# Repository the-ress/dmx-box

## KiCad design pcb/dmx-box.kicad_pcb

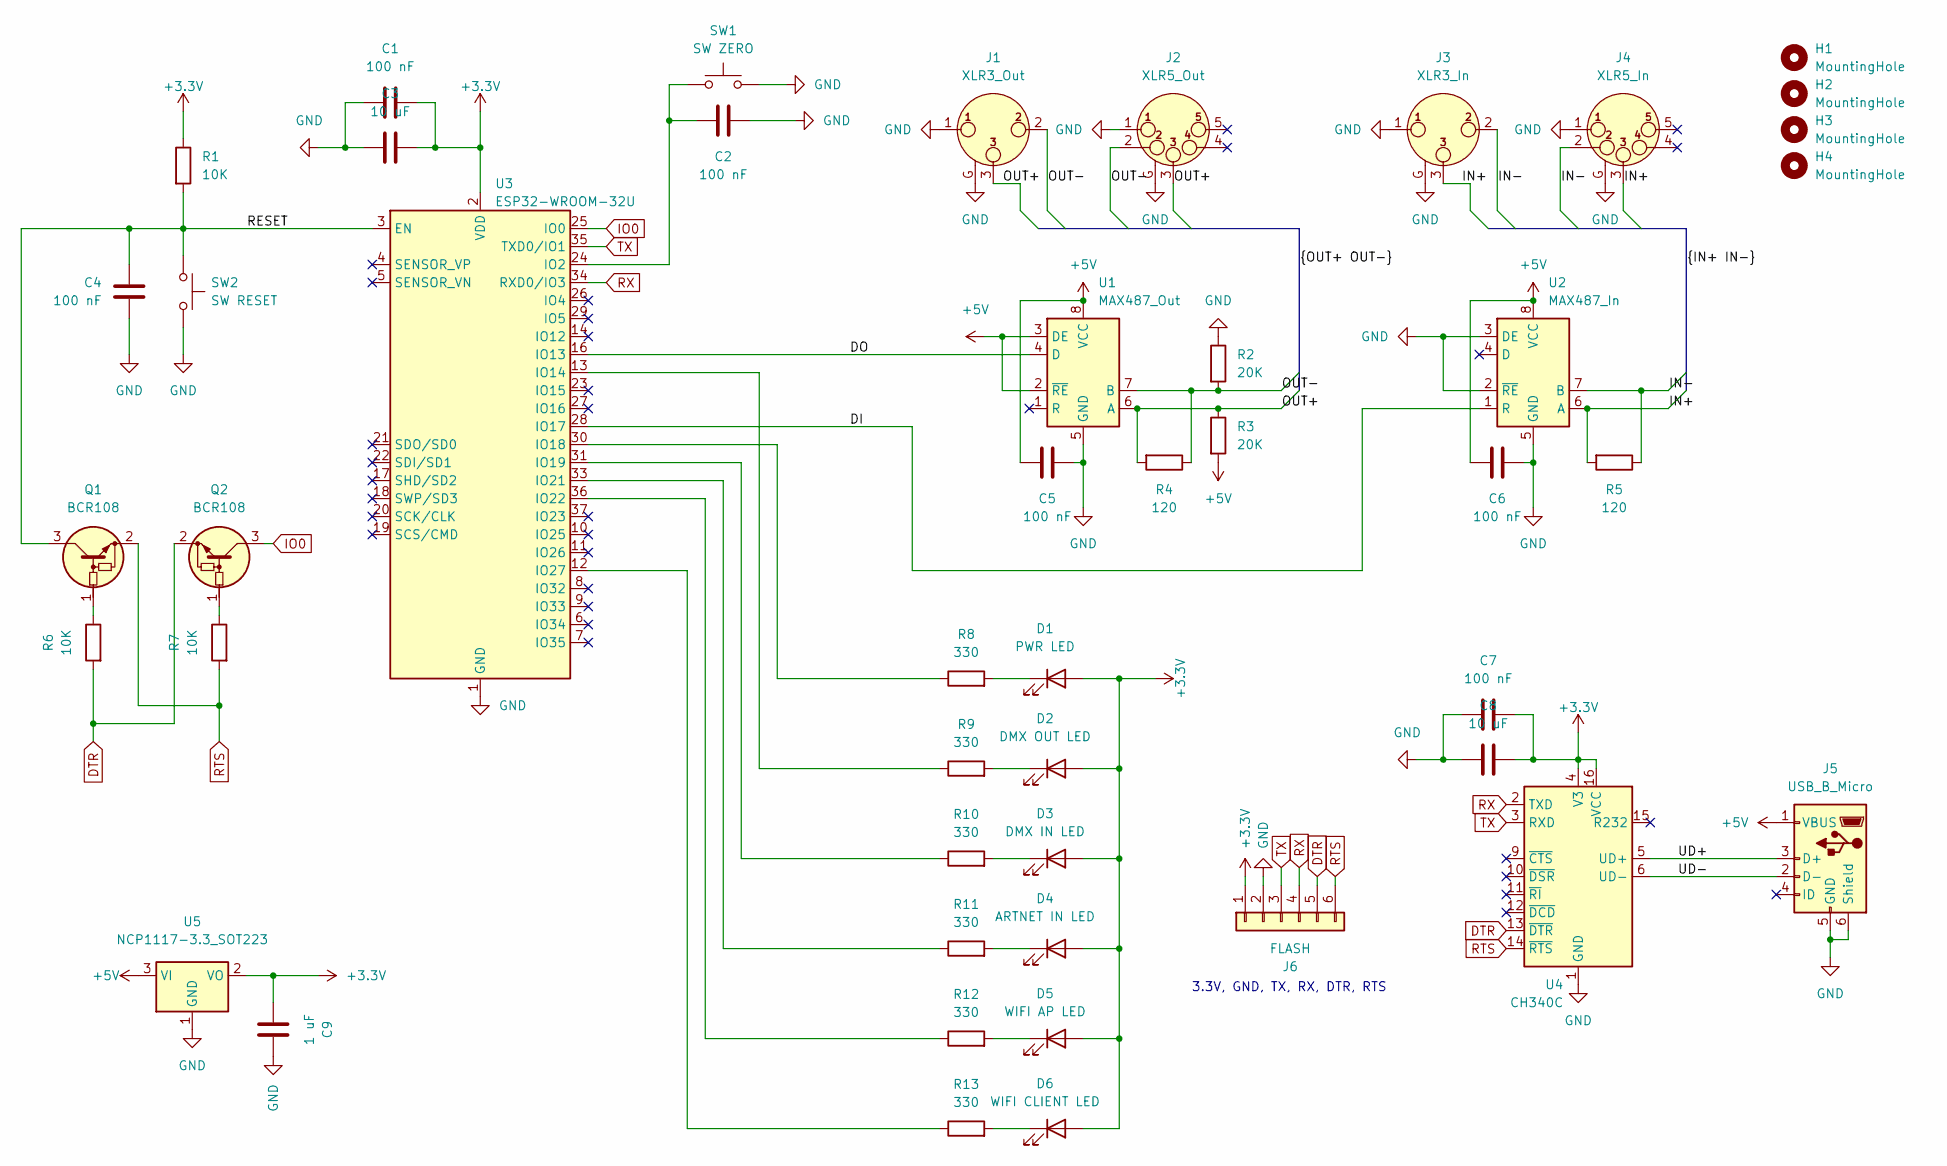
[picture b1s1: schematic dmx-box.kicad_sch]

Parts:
C1, C2, C4, C5, C6, C7: 100 nF; C_0805_2012Metric
C3, C8: 10 uF; C_0805_2012Metric
C9: 1 uF; C_0805_2012Metric
D1: PWR LED; LED_0805_2012Metric
D2: DMX OUT LED; LED_0805_2012Metric
D3: DMX IN LED; LED_0805_2012Metric
D4: ARTNET IN LED; LED_0805_2012Metric
D5: WIFI AP LED; LED_0805_2012Metric
D6: WIFI CLIENT LED; LED_0805_2012Metric
H1, H2, H3, H4: MountingHole; MountingHole_2.5mm
J1: XLR3_Out; Jack_XLR_Neutrik_NC3FAH2_Horizontal
J2: XLR5_Out; Jack_XLR_Neutrik_NC5FAH_Horizontal
J3: XLR3_In; Jack_XLR_Neutrik_NC3MAH_Horizontal
J4: XLR5_In; Jack_XLR_Neutrik_NC5MAH_Horizontal
J5: USB_B_Micro; USB_Micro-B_Molex-105017-0001
J6: FLASH; PinHeader_1x06_P2.54mm_Vertical
Q1, Q2: BCR108; SOT-23
R1, R6, R7: 10K; R_0805_2012Metric
R2, R3: 20K; R_0805_2012Metric
R4, R5: 120; R_0805_2012Metric
R8, R9, R10, R11, R12, R13: 330; R_0805_2012Metric
SW1: SW ZERO; SW_Push_TD-03XA-T
SW2: SW RESET; SW_Push_TD-03XA-T
U1: MAX487_Out; SOIC-8_3.9x4.9mm_P1.27mm
U2: MAX487_In; SOIC-8_3.9x4.9mm_P1.27mm
U3: ESP32-WROOM-32U
U4: CH340C; SOIC-16_3.9x9.9mm_P1.27mm
U5: NCP1117-3.3_SOT223; SOT-223-3_TabPin2

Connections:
+3.3V: C1.2, C3.2, C7.2, C8.2, C9.1, D1.2 (A), D2.2 (A), D3.2 (A), D4.2 (A), D5.2 (A), D6.2 (A), J6.1, R1.1, U3.2 (VDD), U4.4 (V3), U4.16 (VCC), U5.2 (VO)
+5V: C5.1, C6.1, J5.1 (VBUS), R3.2, U1.2 (~RE), U1.3 (DE), U1.8 (VCC), U2.8 (VCC), U5.3 (VI)
/DI: U2.1 (R), U3.28 (IO17)
/DO: U1.4 (D), U3.16 (IO13)
/IN+: J3.3, J4.3, R5.2, U2.6 (A)
/IN-: J3.2, J4.2, R5.1, U2.7 (B)
/OUT+: J1.3, J2.3, R3.1, R4.2, U1.6 (A)
/OUT-: J1.2, J2.2, R2.2, R4.1, U1.7 (B)
/RESET: C4.1, Q1.3 (C), R1.2, SW2.1, U3.3 (EN)
/UD+: J5.3 (D+), U4.5 (UD+)
/UD-: J5.2 (D-), U4.6 (UD-)
DTR: J6.5, Q2.2 (E), R6.2, U4.13 (~DTR)
GND: C1.1, C2.1, C3.1, C4.2, C5.2, C6.2, C7.1, C8.1, C9.2, J1.1, J1.G, J2.1, J2.G, J3.1, J3.G, J4.1, J4.G, J5.5 (GND), J5.6 (Shield), J6.2, R2.1, SW1.2, SW2.2, U1.5 (GND), U2.2 (~RE), U2.3 (DE), U2.5 (GND), U3.1 (GND), U3.15 (GND), U3.38 (GND), U3.39 (GND), U4.1 (GND), U5.1 (GND)
IO0: Q2.3 (C), U3.25 (IO0)
unnamed: D1.1 (K), R8.2
unnamed: D2.1 (K), R9.2
unnamed: D3.1 (K), R10.2
unnamed: D4.1 (K), R11.2
unnamed: D5.1 (K), R12.2
unnamed: D6.1 (K), R13.2
unnamed: Q1.1 (B), R6.1
unnamed: Q2.1 (B), R7.1
unnamed: C2.2, SW1.1, U3.24 (IO2)
unnamed: R9.1, U3.13 (IO14)
unnamed: R8.1, U3.30 (IO18)
unnamed: R10.1, U3.31 (IO19)
unnamed: R11.1, U3.33 (IO21)
unnamed: R12.1, U3.36 (IO22)
unnamed: R13.1, U3.12 (IO27)
RTS: J6.6, Q1.2 (E), R7.2, U4.14 (~RTS)
RX: J6.4, U3.34 (RXD0/IO3), U4.2 (TXD)
TX: J6.3, U3.35 (TXD0/IO1), U4.3 (RXD)

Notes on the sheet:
3.3V, GND, TX, RX, DTR, RTS

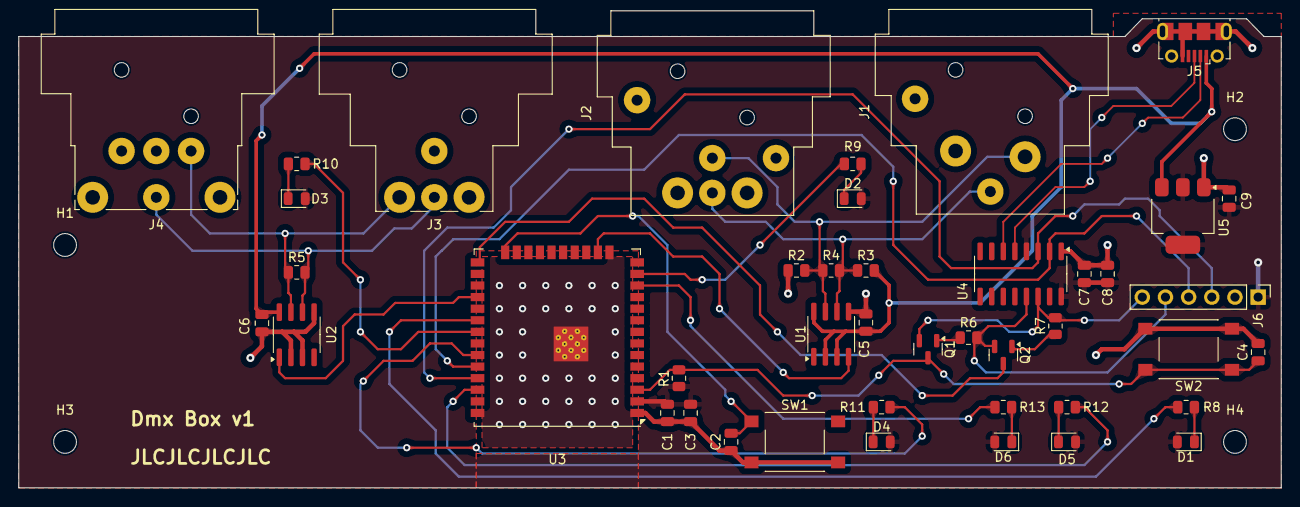
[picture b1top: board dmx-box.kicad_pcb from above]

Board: 2 copper layers, 138.4 x 51.4 mm, 47 parts (0 on the bottom side), 32 nets.

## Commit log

2024-06-28 fix off-by-one
2024-06-28 update things
2024-07-02 add new ui
2024-07-02 ignore artnet poll reply packets
2024-07-06 add components
2024-07-06 upgrade to esp-idf 5.2.2
2024-07-06 remove settings.json
2024-07-06 add sdkconfig
2024-07-06 remove dmxui
2024-07-06 dmxui not a module
2024-07-06 ui makefile
2024-07-06 cleanup
2024-07-06 ignore
2024-07-06 script
2024-07-06 artnet
2024-07-06 refactoring
2024-07-06 format
2024-07-06 add default clang format
2024-07-06 change argument/parameter formatting
2024-07-06 format artnet code
2024-07-06 remove commented out code
2024-07-06 format all c files
2024-07-06 parsing
2024-07-06 storage
2024-07-07 persist hostname
2024-07-07 hostname
2024-07-07 httpd
2024-07-07 more cleanup
2024-07-07 reconnect
2024-07-07 rebust reconnect
2024-07-07 clean up artnet logging
2024-07-07 add dmxbox_ prefix to most symbols
2024-07-07 scan
2024-07-07 websocket scan
2024-07-07 state
2024-07-07 webserver
2024-07-07 wifi
2024-07-07 ap scan
2024-07-08 container
2024-07-08 add effects
2024-07-08 clean up types in effects.c
2024-07-08 fix default wifi name
2024-07-08 initialize storage when flash has been erased
2024-07-09 cleaner
2024-07-09 network list
2024-07-09 cmake
2024-07-09 clangd
2024-07-09 components
2024-07-09 settings
2024-07-09 no headers
2024-07-09 clean
2024-07-09 json
2024-07-09 new api
2024-07-09 add default clang 16 format
2024-07-10 router
2024-07-10 link
2024-07-10 default index
2024-07-10 rename
2024-07-10 more refactoring
2024-07-10 clean up ui cmake
2024-07-10 effects ui
2024-07-10 step
2024-07-11 docker
2024-07-11 container,ui
2024-07-11 support multiple artnet universes
2024-07-12 improve timing
2024-07-12 move stuff into components
2024-07-12 allocate effects dynamically
2024-07-12 fixes
2024-07-12 remove unnecessary precalculated values from effect steps
2024-07-12 remove unnecessary precalculated values from effect steps (correct file)
2024-07-13 fix error handling in dmxbox_api_config_put
2024-07-13 respond to dns queries for configured hostname
2024-07-13 load effect steps from storage
2024-07-13 effect api
2024-07-13 get step
2024-07-13 remove unnecessary `(void)`
2024-07-13 uri parsing
2024-07-13 effects, fix terezas fuckup
2024-07-13 handler limit
2024-07-13 complete
2024-07-13 serializer
2024-07-13 array serializer
2024-07-13 more storage
2024-07-13 dese
2024-07-13 deser
2024-07-14 logging
2024-07-14 put effect step
2024-07-14 validate uri
2024-07-14 effect
2024-07-14 post
2024-07-14 list
2024-07-14 sync effects over espnow
2024-07-14 rest
2024-07-14 send empty
2024-07-14 add alloc helper for storage effect
2024-07-14 create
2024-07-14 refactor
2024-07-15 update loading effects from storage
2024-07-20 enlarge nvs partition
2024-07-20 autosave artnet data to nvs periodically
2024-07-20 skip invalid effects when loading
2024-07-20 add DELETE method for effects
2024-07-20 add configurable universe addresses
2024-07-20 fix list effects with 0 effects
2024-07-20 fix effect step list serialization
2024-07-20 change effect storage struct to packed to fix json serialization
2024-07-20 add PUT effects
2024-07-20 add list and delete effect steps
2024-07-20 separate id for distributed effects from effect id
2024-07-20 add artnet settings ui
2024-07-21 add cors headers everywhere
2024-07-21 ui: disable artnet universe validation
2024-07-21 espnow: support different packet types
2024-07-22 expose artnet universes over http
2024-07-22 move wifi event handling to separate file
2024-07-22 wifi: keep trying to connect as STA
2024-07-24 api: return message in error responses
2024-07-26 support batch PUT for effect steps
2024-07-26 api: add some utility endpoints
2024-07-26 api: make effect rate_channel optional
2024-07-26 add missing include
2024-11-05 add GHA workflow
2024-11-05 set flash size to 16MB
2024-11-05 fix ui build
2024-11-05 install node
2025-03-12 fix build command
2025-03-12 test all leds on startup
2025-04-09 add kicad files
